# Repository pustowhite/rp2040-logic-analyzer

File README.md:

# RP2040 Logic Analyzer

An eight-channel logic analyzer hardware project built around the Raspberry Pi RP2040, with a custom two-layer PCB, USB-C connectivity, and selectable 1.8 V / 3.3 V input logic modes.

I developed this project to gain practical experience in circuit design and PCB layout, from the input interface and power supplies to the microcontroller support circuitry. It is part of my electronics engineering portfolio.

## Hardware overview

| Item | Design |
| --- | --- |
| Microcontroller | Raspberry Pi RP2040 |
| Digital inputs | 8 channels |
| Intended input logic modes | 1.8 V and 3.3 V, selected by a physical switch |
| Input level translator | SN74LVC8T245 |
| Input protection components | Two SRV05-4 arrays |
| Input connector | 2 x 8, 2.54 mm header, with alternating signal and ground pins |
| USB connector | TYPEC-304-ACP16 |
| USB protection component | USBLC6-2SC6 |
| External program memory | W25Q32JVSS |
| Power | USB 5 V input; TLV75533PDBV and TLV75518PDBV regulators |
| Debug interface | Four-pin SWD header |
| PCB | Two copper layers; 79.7 x 50.7 mm outline in the included layout |
| CAD | KiCad 10.0, as recorded in the source files |

The voltage modes describe the intended logic families. Input thresholds, maximum reliable signal frequency, and protection performance still require verification on the assembled board.

## How it work

Eight external digital signals enter through the input header. The input network and SN74LVC8T245 interface these signals to the RP2040's 3.3 V domain. USB-C supplies power and provides the physical connection to the host computer.

The planned capture implementation uses the RP2040's programmable I/O (PIO) to sample the inputs and direct memory access (DMA) to move samples into RAM. Capture firmware and host software are not included in this snapshot. Sampling rate, capture depth, trigger functions, and protocol decoding are therefore not presented as implemented features.

## Engineering work

The project brings together several parts of a complete PCB design:

- An eight-channel input interface with selectable translator supply voltage.
- RP2040 support circuitry, external flash, a crystal, and local decoupling.
- USB-C power and data connections with protection components.
- Component placement, signal routing, and ground copper on a two-layer board.
- Integration of a custom connector symbol and footprint into a portable KiCad project.

Component documentation describes the individual devices; it does not establish the measured performance of this board.

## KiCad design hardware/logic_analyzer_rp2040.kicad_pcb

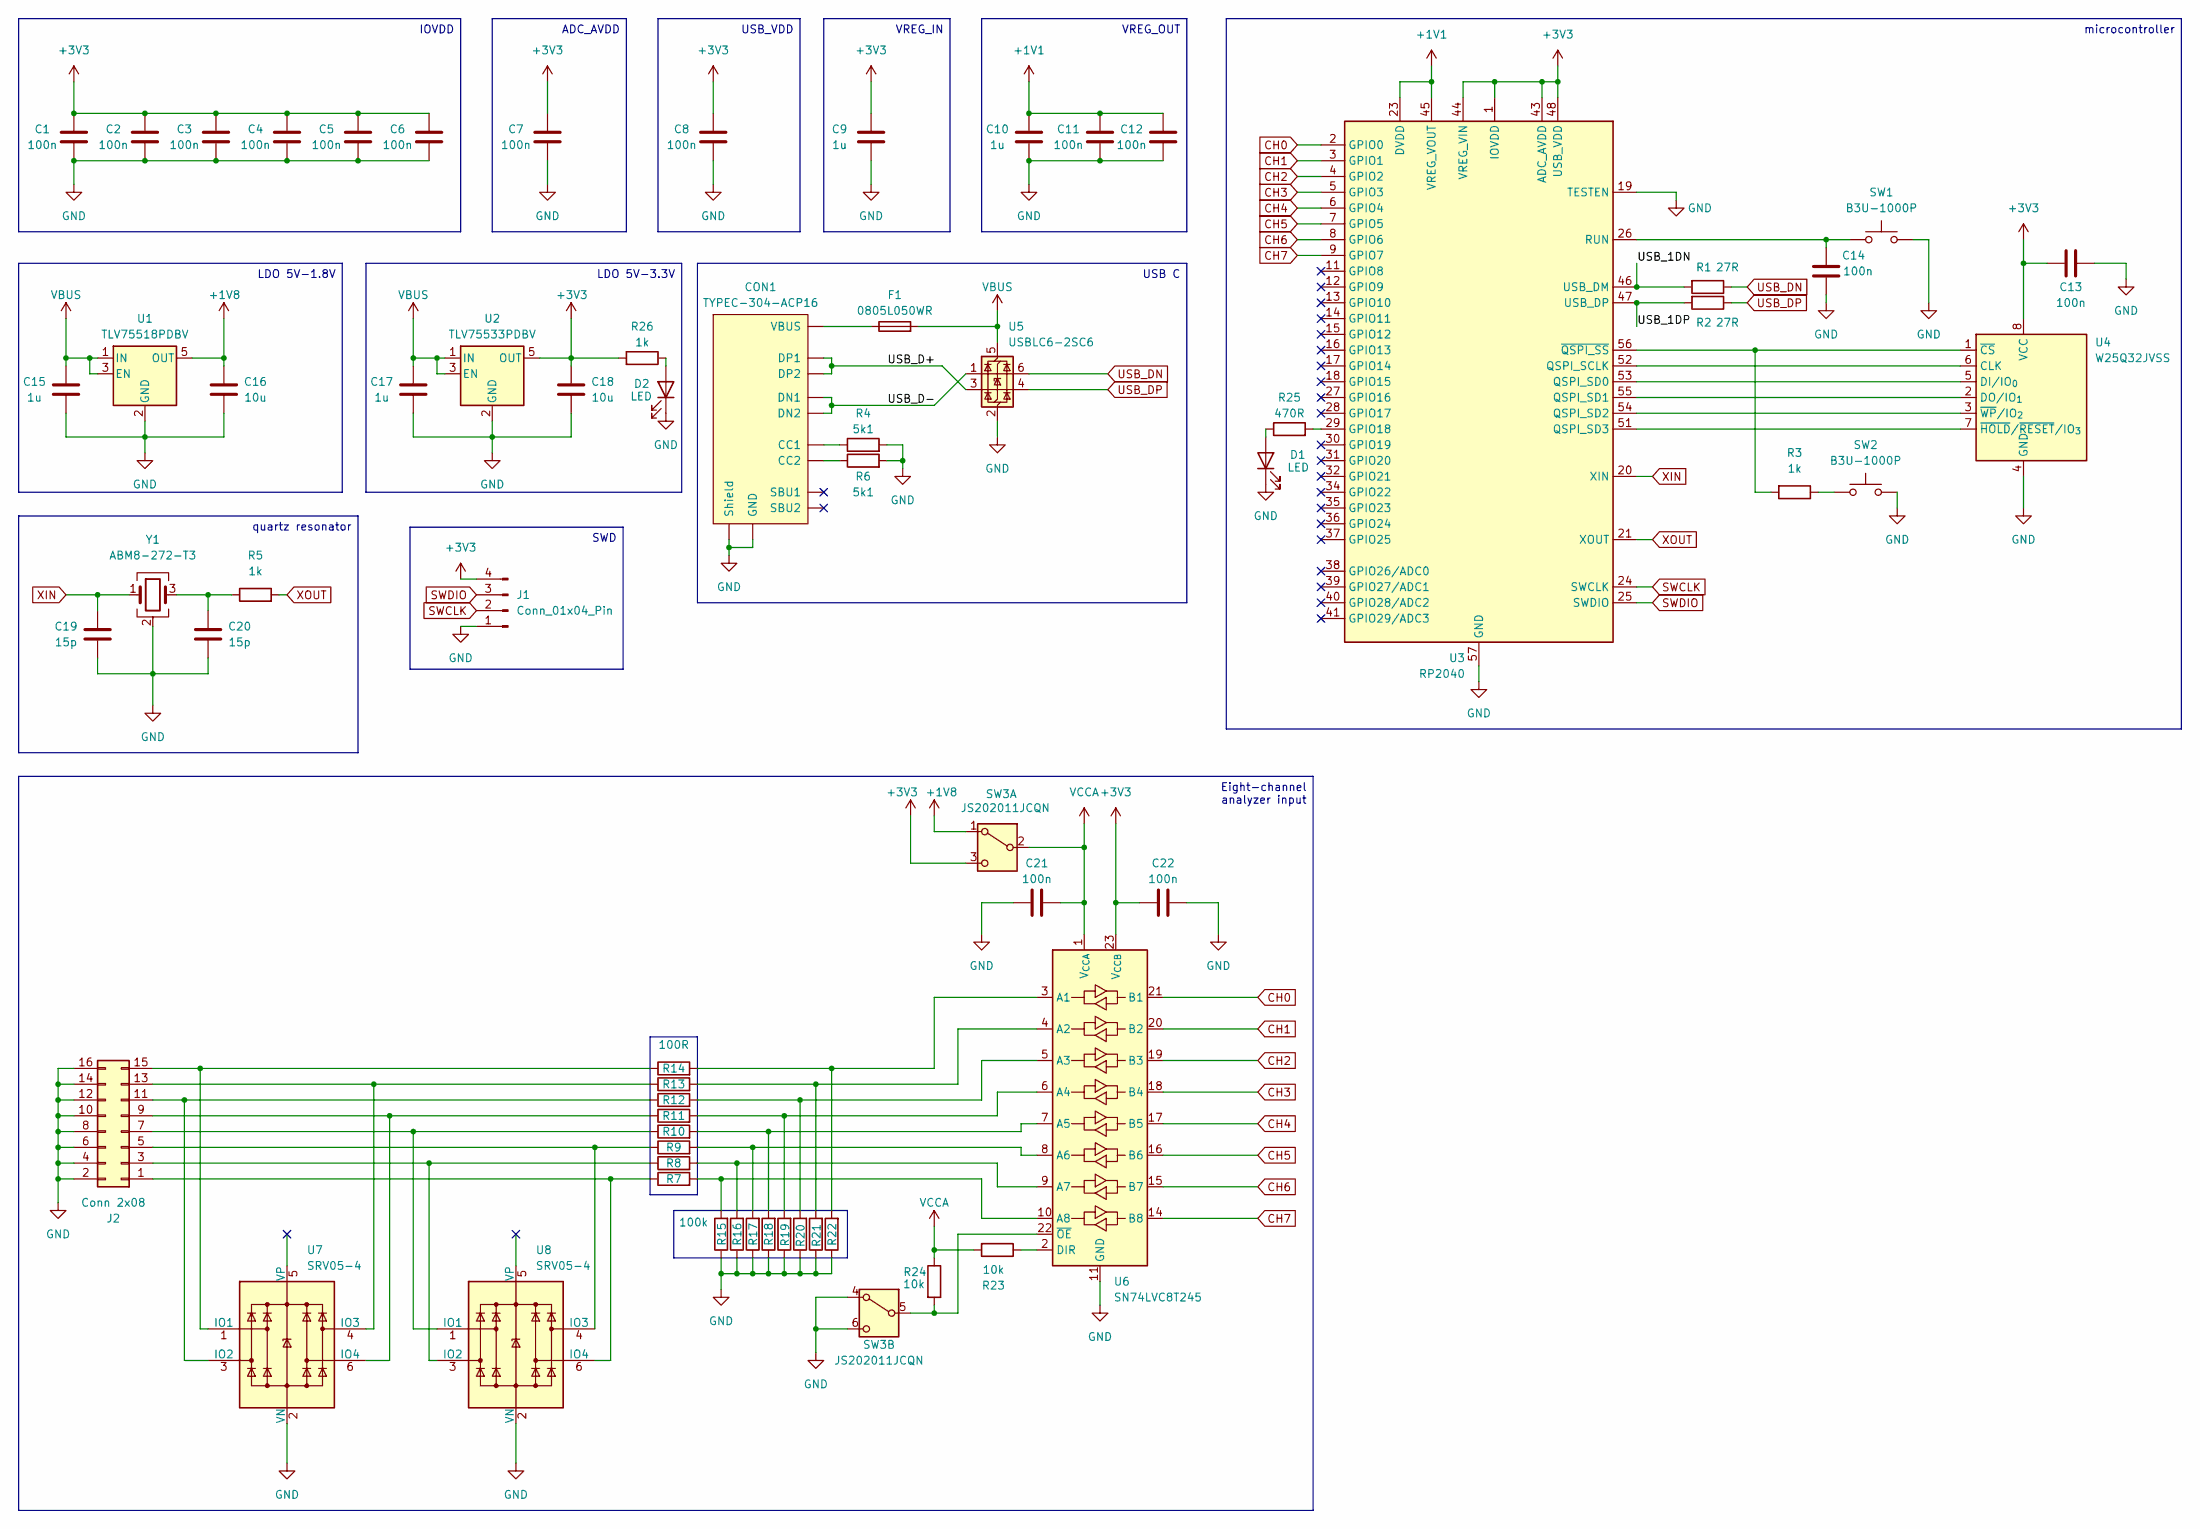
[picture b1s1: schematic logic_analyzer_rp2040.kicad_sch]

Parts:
C1, C2, C3, C4, C5, C6, C7, C8, C11, C12, C13, C14, C21, C22: 100n; C_0402_1005Metric
C9, C10, C15, C17: 1u; C_0603_1608Metric
C16, C18: 10u; C_0603_1608Metric
C19, C20: 15p; C_0603_1608Metric
CON1: TYPEC-304-ACP16; LCSC C2982555
D1, D2: LED; LED_0603_1608Metric
F1: 0805L050WR; Fuse_0805_2012Metric
J1: Conn_01x04_Pin; PinHeader_1x04_P2.54mm_Vertical
J2: Conn 2x08; PinHeader_2x08_P2.54mm_Vertical
R1, R2: 27R; R_0603_1608Metric
R3, R5, R26: 1k; R_0603_1608Metric
R4, R6: 5k1; R_0603_1608Metric
R7, R8, R9, R10, R11, R12, R13, R14: 100R; R_0603_1608Metric
R15, R16, R17, R18, R19, R20, R21, R22: 100k; R_0603_1608Metric
R23, R24: 10k; R_0603_1608Metric
R25: 470R; R_0603_1608Metric
SW1, SW2: B3U-1000P; SW_SPST_B3U-1000P
SW3: JS202011JCQN; SW_DPDT_CK_JS202011JCQN
U1: TLV75518PDBV; SOT-23-5
U2: TLV75533PDBV; SOT-23-5
U3: RP2040; QFN-56-1EP_7x7mm_P0.4mm_EP3.2x3.2mm
U4: W25Q32JVSS; SOIC-8_5.3x5.3mm_P1.27mm
U5: USBLC6-2SC6; SOT-23-6
U6: SN74LVC8T245; TSSOP-24_4.4x7.8mm_P0.65mm
U7, U8: SRV05-4; SOT-23-6
Y1: ABM8-272-T3; Crystal_SMD_3225-4Pin_3.2x2.5mm

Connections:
+1V1: C10.2, C11.2, C12.2, U3.23 (DVDD), U3.45 (VREG_VOUT), U3.50 (DVDD)
+1V8: C16.2, SW3.1 (A), U1.5 (OUT); also elsewhere on the board
+3V3: C1.2, C2.2, C3.2, C4.2, C5.2, C6.2, C7.2, C8.2, C9.2, C13.2, C18.2, C22.1, J1.4, R26.2, SW3.3 (C), U2.5 (OUT), U3.1 (IOVDD), U3.10 (IOVDD), U3.22 (IOVDD), U3.33 (IOVDD), U3.42 (IOVDD), U3.43 (ADC_AVDD), U3.44 (VREG_VIN), U3.48 (USB_VDD), U3.49 (IOVDD), U4.8 (VCC), U6.23 (V_{CCB}), U6.24 (V_{CCB}); also elsewhere on the board
/USB_1DN: R1.2, U3.46 (USB_DM)
/USB_1DP: R2.2, U3.47 (USB_DP)
/USB_D+: CON1.A6 (DP1), CON1.B6 (DP2), U5.3 (I/O2)
/USB_D-: CON1.A7 (DN1), CON1.B7 (DN2), U5.1 (I/O1)
CH0: U3.2 (GPIO0), U6.21 (B1)
CH1: U3.3 (GPIO1), U6.20 (B2)
CH2: U3.4 (GPIO2), U6.19 (B3)
CH3: U3.5 (GPIO3), U6.18 (B4)
CH4: U3.6 (GPIO4), U6.17 (B5)
CH5: U3.7 (GPIO5), U6.16 (B6)
CH6: U3.8 (GPIO6), U6.15 (B7)
CH7: U3.9 (GPIO7), U6.14 (B8)
GND: C1.1, C2.1, C3.1, C4.1, C5.1, C6.1, C7.1, C8.1, C9.1, C10.1, C11.1, C12.1, C13.1, C14.1, C15.1, C16.1, C17.1, C18.1, C19.2, C20.1, C21.1, C22.2, CON1.GND1 (GND), CON1.GND2 (GND), CON1.S1 (Shield), CON1.S2 (Shield), CON1.S3 (Shield), CON1.S4 (Shield), D1.1 (K), D2.1 (K), J1.1, J2.2, J2.4, J2.6, J2.8, J2.10, J2.12, J2.14, J2.16, R4.2, R6.2, R15.1, R16.1, R17.1, R18.1, R19.1, R20.1, R21.1, R22.1, SW1.1, SW2.1, SW3.4 (A), SW3.6 (C), U1.2 (GND), U2.2 (GND), U3.19 (TESTEN), U3.57 (GND), U4.4 (GND), U5.2 (GND), U6.11 (GND), U6.12 (GND), U6.13 (GND), U7.2 (VN), U8.2 (VN), Y1.2 (G), Y1.4 (G); also elsewhere on the board
unnamed: C20.2, R5.1, Y1.3
unnamed: CON1.A5 (CC1), R4.1
unnamed: CON1.B5 (CC2), R6.1
unnamed: CON1.VBUS1 (VBUS), CON1.VBUS2 (VBUS), F1.1
unnamed 20: D1.2 (A), R25.1; also elsewhere on the board
unnamed 21: D2.2 (A), R26.1; also elsewhere on the board
unnamed: J2.1, R7.1, U8.6 (IO4)
unnamed: J2.3, R8.1, U8.3 (IO2)
unnamed: J2.5, R9.1, U8.4 (IO3)
unnamed: J2.7, R10.1, U8.1 (IO1)
unnamed: J2.9, R11.1, U7.6 (IO4)
unnamed: J2.11, R12.1, U7.3 (IO2)
unnamed: J2.13, R13.1, U7.4 (IO3)
unnamed: J2.15, R14.1, U7.1 (IO1)
unnamed 30: R3.1, SW2.2; also elsewhere on the board
unnamed 31: R24.2, SW3.5 (B), U6.22 (~OE); also elsewhere on the board
unnamed: R25.2, U3.29 (GPIO18)
unnamed: U3.52 (QSPI_SCLK), U4.6 (CLK)
unnamed: U3.53 (QSPI_SD0), U4.5 (DI/IO_{0})
unnamed: U3.55 (QSPI_SD1), U4.2 (DO/IO_{1})
unnamed: U3.54 (QSPI_SD2), U4.3 (~WP/IO_{2})
unnamed: U3.51 (QSPI_SD3), U4.7 (~HOLD/~RESET/IO_{3})
unnamed 38: C14.2, SW1.2, U3.26 (RUN); also elsewhere on the board
unnamed: R3.2, U3.56 (~QSPI_SS), U4.1 (~CS)
unnamed: R14.2, R22.2, U6.3 (A1)
unnamed: R13.2, R21.2, U6.4 (A2)
unnamed: R12.2, R20.2, U6.5 (A3)
unnamed: R11.2, R19.2, U6.6 (A4)
unnamed: R10.2, R18.2, U6.7 (A5)
unnamed: R9.2, R17.2, U6.8 (A6)
unnamed: R8.2, R16.2, U6.9 (A7)
unnamed: R7.2, R15.2, U6.10 (A8)
unnamed: R23.1, U6.2 (DIR)
SWCLK: J1.2, U3.24 (SWCLK); also elsewhere on the board
SWDIO: J1.3, U3.25 (SWDIO); also elsewhere on the board
USB_DN: R1.1, U5.6 (I/O1)
USB_DP: R2.1, U5.4 (I/O2)
VBUS: C15.2, C17.2, F1.2, U1.1 (IN), U1.3 (EN), U2.1 (IN), U2.3 (EN), U5.5 (VBUS)
VCCA: C21.2, R23.2, R24.1, SW3.2 (B), U6.1 (V_{CCA}); also elsewhere on the board
XIN: C19.1, U3.20 (XIN), Y1.1
XOUT: R5.2, U3.21 (XOUT)

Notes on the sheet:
LDO 5V-3.3V
USB C
SWD
IOVDD
ADC_AVDD
VREG_IN
VREG_OUT
LDO 5V-1.8V
quartz resonator
microcontroller
USB_VDD
Eight-channel analyzer input

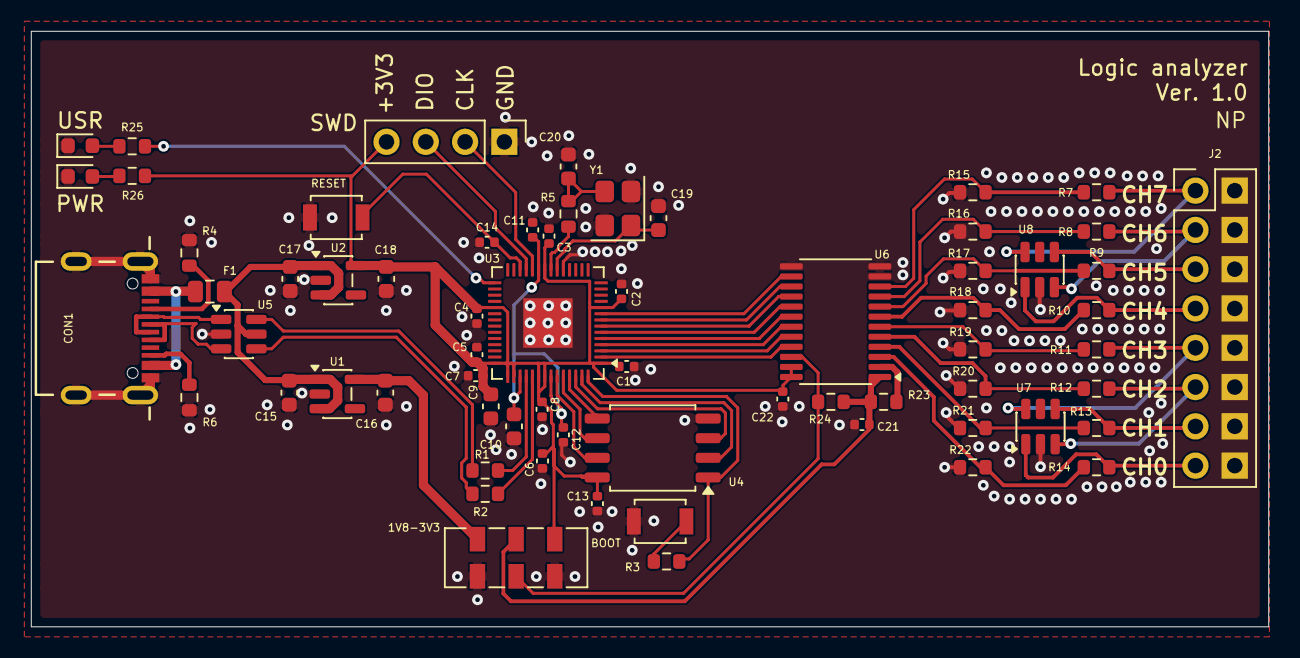
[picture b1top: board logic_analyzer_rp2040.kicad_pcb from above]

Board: 2 copper layers, 80.0 x 38.5 mm, 66 parts (0 on the bottom side), 57 nets.

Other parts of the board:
1V8-3V3: JS202011JCQN; SW_DPDT_CK_JS202011JCQN
BOOT: B3U-1000P; SW_SPST_B3U-1000P
PWR: LED; LED_0603_1608Metric
RESET: B3U-1000P; SW_SPST_B3U-1000P
SWD: Conn_01x04_Pin; PinHeader_1x04_P2.54mm_Vertical
USR: LED; LED_0603_1608Metric

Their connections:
+1V8: 1V8-3V3.1 (A); also elsewhere on the board
+3V3: 1V8-3V3.3 (C), SWD.4; also elsewhere on the board
GND: 1V8-3V3.4 (A), 1V8-3V3.6 (C), BOOT.1, PWR.1 (K), RESET.1, SWD.1, USR.1 (K); also elsewhere on the board
unnamed 20: USR.2 (A); also elsewhere on the board
unnamed 21: PWR.2 (A); also elsewhere on the board
unnamed 30: BOOT.2; also elsewhere on the board
unnamed 31: 1V8-3V3.5 (B); also elsewhere on the board
unnamed 38: RESET.2; also elsewhere on the board
SWCLK: SWD.2; also elsewhere on the board
SWDIO: SWD.3; also elsewhere on the board
VCCA: 1V8-3V3.2 (B); also elsewhere on the board
